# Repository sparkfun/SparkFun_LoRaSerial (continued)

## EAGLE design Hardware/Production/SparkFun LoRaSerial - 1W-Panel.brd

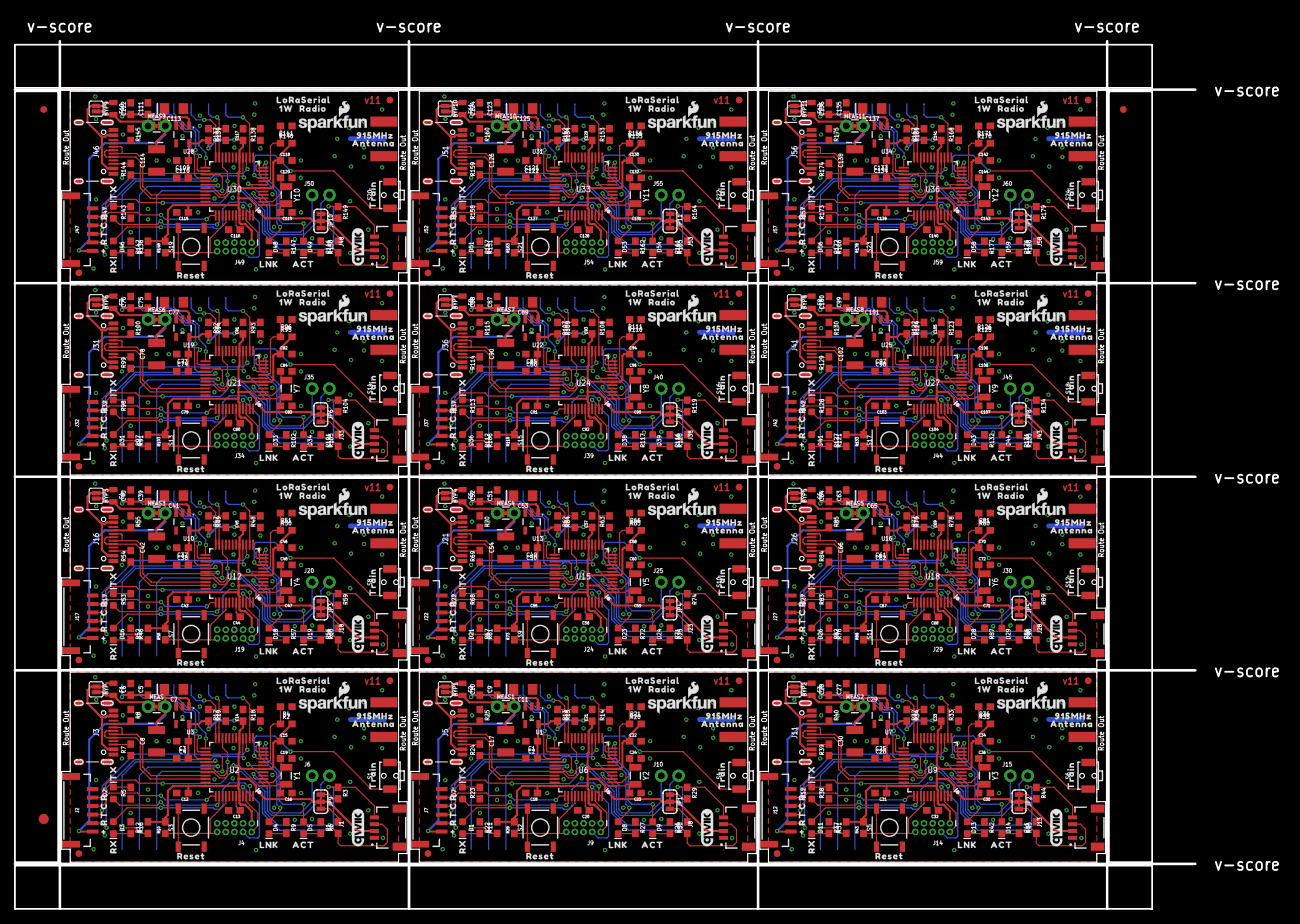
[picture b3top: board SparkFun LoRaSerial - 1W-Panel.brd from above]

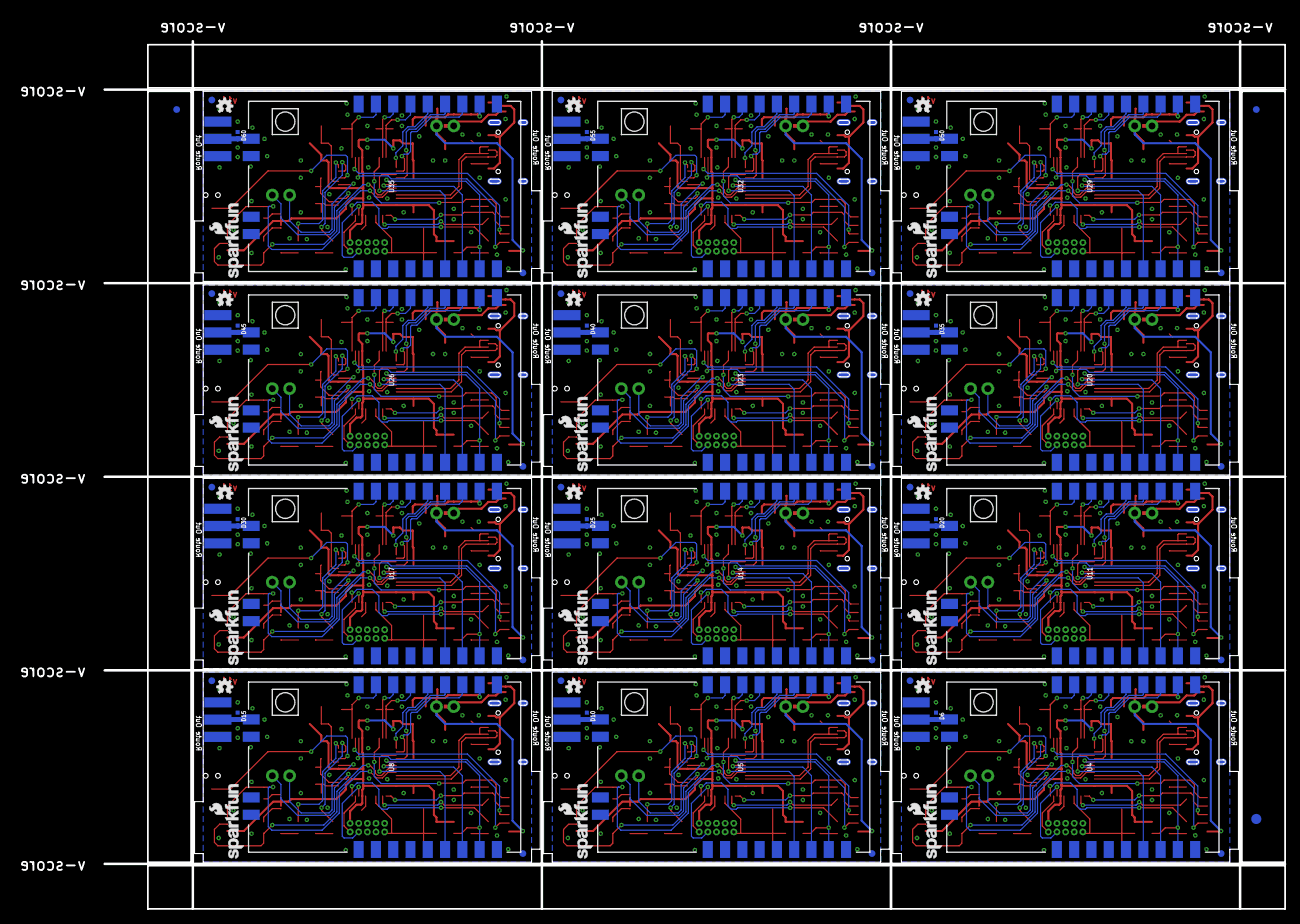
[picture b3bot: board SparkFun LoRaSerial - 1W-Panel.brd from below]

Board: 2 copper layers, 173.5 x 127.5 mm, 882 parts (87 on the bottom side), 540 nets.

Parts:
BYP, BYP1, BYP2, BYP3, BYP4, BYP5, BYP6, BYP7, BYP8, BYP9, BYP10, BYP11: JUMPER-SMT_2_NO_SILK; SMT-JUMPER_2_NO_SILK
C1, C3, C25, C37, C49, C61, C73, C85, C97, C109, C121, C133: 1.0uF; 0603
C2, C4, C6, C10, C12, C13, C14, C15, C18, C20, C21, C22, C26, C28, C31, C32, C33, C34, C38, C40, C43, C44, C45, C46, C50, C52, C55, C56, C57, C58, C62, C64, C67, C68, C69, C70, C74, C76, C79, C80, C81, C82, C86, C88, C91, C92, C93, C94, C98, C100, C103, C104, C105, C106, C110, C112, C115, C116, C117, C118, C122, C124, C127, C128, C129, C130, C134, C136, C139, C140, C141, C142: 0.1uF; 0603
C5, C9, C27, C39, C51, C63, C75, C87, C99, C111, C123, C135: 0.22uF; 0603
C7, C11, C29, C41, C53, C65, C77, C89, C101, C113, C125, C137: 10uF; EIA3216
C8, C17, C30, C42, C54, C66, C78, C90, C102, C114, C126, C138: 47uF; EIA3528
C16, C19, C23, C24, C35, C36, C47, C48, C59, C60, C71, C72, C83, C84, C95, C96, C107, C108, C119, C120, C131, C132, C143, C144: 15pF; 0603
D1, D3, D11, D16, D21, D26, D31, D36, D41, D46, D51, D56: Yellow; LED-0603
D2, D7, D12, D17, D22, D27, D32, D37, D42, D47, D52, D57: GREEN; LED-0603
D4, D8, D13, D18, D23, D28, D33, D38, D43, D48, D53, D58: BLUE; LED-0603
D5, D9, D14, D19, D24, D29, D34, D39, D44, D49, D54, D59: RED; LED-0603
D6, D10, D15, D20, D25, D30, D35, D40, D45, D50, D55, D60: PESD0402; 0402-TIGHT
E1, E2, E3, E4, E5, E6, E7, E8, E9, E10, E11, E12: RP-SMA; RP-SMA-EDGE
E$1, E$2, E$3, E$4: FIDUCIAL-1X2
E$5, E$6: FIDUCIAL-1.5X3
F1, F2, F3, F4, F5, F6, F7, F8, F9, F10, F11, F12: 6V 0.5A; 0805
FID1, FID2, FID3, FID4, FID5, FID6, FID7, FID8, FID9, FID10, FID11, FID12, FID13, FID14, FID15, FID16, FID17, FID18, FID19, FID20, FID21, FID22, FID23, FID24, FID25, FID26, FID27, FID28, FID29, FID30, FID31, FID32, FID33, FID34, FID35, FID36, FID37, FID38, FID39, FID40, FID41, FID42, FID43, FID44, FID45, FID46, FID47, FID48: FIDUCIAL1X2; FIDUCIAL-1X2
J1, J8, J13, J18, J23, J28, J33, J38, J43, J48, J53, J58: QWIIC_RIGHT_ANGLE; JST04_1MM_RA
J2, J7, J12, J17, J22, J27, J32, J37, J42, J47, J52, J57: JST-6-SMD-1.25MM-LOCKING
J3, J5, J11, J16, J21, J26, J31, J36, J41, J46, J51, J56: USB C; USB-C-16P
J4, J9, J14, J19, J24, J29, J34, J39, J44, J49, J54, J59: JTAG; 2X5-PTH-1.27MM-NO_SILK
J6, J10, J15, J20, J25, J30, J35, J40, J45, J50, J55, J60: 1X02_NO_SILK
JP1, JP2, JP3, JP4, JP5, JP6, JP7, JP8, JP9, JP10, JP11, JP12: JUMPER-SMT_3_2-NC_TRACE_SILK; SMT-JUMPER_3_2-NC_TRACE_SILK
LOGO1, LOGO5, LOGO9, LOGO13, LOGO17, LOGO21, LOGO25, LOGO29, LOGO33, LOGO37, LOGO41, LOGO45: SFE_LOGO_NAME_FLAME10_MM; SFE_LOGO_NAME_FLAME_10MM
LOGO2, LOGO6, LOGO10, LOGO14, LOGO18, LOGO22, LOGO26, LOGO30, LOGO34, LOGO38, LOGO42, LOGO46: SFE_LOGO_NAME_FLAME.1_INCH; SFE_LOGO_NAME_FLAME_.1
LOGO3, LOGO8, LOGO12, LOGO16, LOGO20, LOGO24, LOGO28, LOGO32, LOGO36, LOGO40, LOGO44, LOGO48: QWIIC_LOGO_CONNECTOR; QWIIC_5.5MM
LOGO4, LOGO7, LOGO11, LOGO15, LOGO19, LOGO23, LOGO27, LOGO31, LOGO35, LOGO39, LOGO43, LOGO47: OSHW-LOGOMINI; OSHW-LOGO-MINI
MEAS, MEAS1, MEAS2, MEAS3, MEAS4, MEAS5, MEAS6, MEAS7, MEAS8, MEAS9, MEAS10, MEAS11: JUMPER-COMBO_2_NC_TRACE; COMBO-JUMPER_2_NC_TRACE
R1, R9, R26, R27, R41, R42, R56, R57, R71, R72, R86, R87, R101, R102, R116, R117, R131, R132, R146, R147, R161, R162, R176, R177: 1k; 0603
R2, R4, R10, R20, R21, R28, R35, R36, R43, R50, R51, R58, R65, R66, R73, R80, R81, R88, R95, R96, R103, R110, R111, R118, R125, R126, R133, R140, R141, R148, R155, R156, R163, R170, R171, R178: 10k; 0603
R3, R6, R29, R30, R44, R45, R59, R60, R74, R75, R89, R90, R104, R105, R119, R120, R134, R135, R149, R150, R164, R165, R179, R180: 2.2k; 0603
R5, R12, R22, R23, R37, R38, R52, R53, R67, R68, R82, R83, R97, R98, R112, R113, R127, R128, R142, R143, R157, R158, R172, R173: 4.7k; 0603
R7, R8, R24, R25, R39, R40, R54, R55, R69, R70, R84, R85, R99, R100, R114, R115, R129, R130, R144, R145, R159, R160, R174, R175: 5.1k; 0603
R11, R13, R14, R15, R16, R17, R18, R19, R31, R32, R33, R34, R46, R47, R48, R49, R61, R62, R63, R64, R76, R77, R78, R79, R91, R92, R93, R94, R106, R107, R108, R109, R121, R122, R123, R124, R136, R137, R138, R139, R151, R152, R153, R154, R166, R167, R168, R169: 100k; 0603
S1, S4, S6, S8, S10, S12, S14, S16, S18, S20, S22, S24: Train; TACTILE_SWITCH_SMD_RIGHT_ANGLE
S2, S3, S5, S7, S9, S11, S13, S15, S17, S19, S21, S23: Reset; TACTILE_SWITCH_SMD_5.2MM
U1, U3, U7, U10, U13, U16, U19, U22, U25, U28, U31, U34: AP2112K-3.3; SOT23-5
U2, U6, U9, U12, U15, U18, U21, U24, U27, U30, U33, U36: ATSAMD21G-A; TQFP-48
U4, U5, U8, U11, U14, U17, U20, U23, U26, U29, U32, U35: E19-915M30S; E19-915MS1W
U$1, U$33, U$50, U$67, U$84, U$101, U$118, U$135, U$152, U$169, U$186, U$203: 1W1
U$2, U$8, U$35, U$52, U$69, U$86, U$103, U$120, U$137, U$154, U$171, U$188: RESET0
U$3, U$19, U$36, U$53, U$70, U$87, U$104, U$121, U$138, U$155, U$172, U$189: 915MHZ0
U$4, U$34, U$51, U$68, U$85, U$102, U$119, U$136, U$153, U$170, U$187, U$204: TRAIN0
U$5, U$21, U$38, U$55, U$72, U$89, U$106, U$123, U$140, U$157, U$174, U$191: RADIO2
U$6, U$22, U$39, U$56, U$73, U$90, U$107, U$124, U$141, U$158, U$175, U$192: ACT3
U$7, U$23, U$40, U$57, U$74, U$91, U$108, U$125, U$142, U$159, U$176, U$193: LNK2
U$9, U$20, U$37, U$54, U$71, U$88, U$105, U$122, U$139, U$156, U$173, U$190: ANTENNA1
U$10, U$24, U$41, U$58, U$75, U$92, U$109, U$126, U$143, U$160, U$177, U$194: RX1
U$11, U$25, U$42, U$59, U$76, U$93, U$110, U$127, U$144, U$161, U$178, U$195: TX0
U$12, U$26, U$43, U$60, U$77, U$94, U$111, U$128, U$145, U$162, U$179, U$196: #0
U$13, U$27, U$44, U$61, U$78, U$95, U$112, U$129, U$146, U$163, U$180, U$197: #1
U$14, U$28, U$45, U$62, U$79, U$96, U$113, U$130, U$147, U$164, U$181, U$198: R3
U$15, U$29, U$46, U$63, U$80, U$97, U$114, U$131, U$148, U$165, U$182, U$199: T2
U$16, U$30, U$47, U$64, U$81, U$98, U$115, U$132, U$149, U$166, U$183, U$200: C0
U$17, U$31, U$48, U$65, U$82, U$99, U$116, U$133, U$150, U$167, U$184, U$201: R1
U$18, U$32, U$49, U$66, U$83, U$100, U$117, U$134, U$151, U$168, U$185, U$202: LORASERIAL0
Y1, Y2, Y3, Y4, Y5, Y6, Y7, Y8, Y9, Y10, Y11, Y12: 32.768kHz; CRYSTAL-SMD-3.2X1.5MM

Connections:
3.3V: C3.1, C4.2, C12.1, C14.1, C15.1, J1.2, J4.1, JP9.2, R2.2, R10.2, R16.2, R17.2, U2.6, U2.17, U2.36, U2.44, U3.5
3.3V1: C1.1, C2.2, C18.1, C21.1, C22.1, J8.2, J9.1, JP1.2, R11.2, R13.2, R20.2, R28.2, U1.5, U6.6, U6.17, U6.36, U6.44
3.3V2: C25.1, C26.2, C31.1, C33.1, C34.1, J13.2, J14.1, JP2.2, R31.2, R32.2, R35.2, R43.2, U7.5, U9.6, U9.17, U9.36, U9.44
3.3V3: C37.1, C38.2, C43.1, C45.1, C46.1, J18.2, J19.1, JP3.2, R46.2, R47.2, R50.2, R58.2, U10.5, U12.6, U12.17, U12.36, U12.44
3.3V4: C49.1, C50.2, C55.1, C57.1, C58.1, J23.2, J24.1, JP4.2, R61.2, R62.2, R65.2, R73.2, U13.5, U15.6, U15.17, U15.36, U15.44
3.3V5: C61.1, C62.2, C67.1, C69.1, C70.1, J28.2, J29.1, JP5.2, R76.2, R77.2, R80.2, R88.2, U16.5, U18.6, U18.17, U18.36, U18.44
3.3V6: C73.1, C74.2, C79.1, C81.1, C82.1, J33.2, J34.1, JP6.2, R91.2, R92.2, R95.2, R103.2, U19.5, U21.6, U21.17, U21.36, U21.44
3.3V7: C85.1, C86.2, C91.1, C93.1, C94.1, J38.2, J39.1, JP7.2, R106.2, R107.2, R110.2, R118.2, U22.5, U24.6, U24.17, U24.36, U24.44
3.3V8: C97.1, C98.2, C103.1, C105.1, C106.1, J43.2, J44.1, JP8.2, R121.2, R122.2, R125.2, R133.2, U25.5, U27.6, U27.17, U27.36, U27.44
3.3V9: C109.1, C110.2, C115.1, C117.1, C118.1, J48.2, J49.1, JP10.2, R136.2, R137.2, R140.2, R148.2, U28.5, U30.6, U30.17, U30.36, U30.44
3.3V10: C121.1, C122.2, C127.1, C129.1, C130.1, J53.2, J54.1, JP11.2, R151.2, R152.2, R155.2, R163.2, U31.5, U33.6, U33.17, U33.36, U33.44
3.3V11: C133.1, C134.2, C139.1, C141.1, C142.1, J58.2, J59.1, JP12.2, R166.2, R167.2, R170.2, R178.2, U34.5, U36.6, U36.17, U36.36, U36.44
5V: C5.1, C6.1, C7.+, C8.A, J2.6, MEAS.2, MEAS.4, U3.1, U3.3, U4.11
5V1: C9.1, C10.1, C11.+, C17.A, J7.6, MEAS1.2, MEAS1.4, U1.1, U1.3, U5.11
5V2: C27.1, C28.1, C29.+, C30.A, J12.6, MEAS2.2, MEAS2.4, U7.1, U7.3, U8.11
5V3: C39.1, C40.1, C41.+, C42.A, J17.6, MEAS3.2, MEAS3.4, U10.1, U10.3, U11.11
5V4: C51.1, C52.1, C53.+, C54.A, J22.6, MEAS4.2, MEAS4.4, U13.1, U13.3, U14.11
5V5: C63.1, C64.1, C65.+, C66.A, J27.6, MEAS5.2, MEAS5.4, U16.1, U16.3, U17.11
5V6: C75.1, C76.1, C77.+, C78.A, J32.6, MEAS6.2, MEAS6.4, U19.1, U19.3, U20.11
5V7: C87.1, C88.1, C89.+, C90.A, J37.6, MEAS7.2, MEAS7.4, U22.1, U22.3, U23.11
5V8: C99.1, C100.1, C101.+, C102.A, J42.6, MEAS8.2, MEAS8.4, U25.1, U25.3, U26.11
5V9: C111.1, C112.1, C113.+, C114.A, J47.6, MEAS9.2, MEAS9.4, U28.1, U28.3, U29.11
5V10: C123.1, C124.1, C125.+, C126.A, J52.6, MEAS10.2, MEAS10.4, U31.1, U31.3, U32.11
5V11: C135.1, C136.1, C137.+, C138.A, J57.6, MEAS11.2, MEAS11.4, U34.1, U34.3, U35.11
A0: J6.2, U2.3
A1: J6.1, U2.7
A2: J10.1, U6.7
A2/BOARD_ID: R2.1, R4.2, U2.8
A2/BOARD_ID1: R20.1, R21.2, U6.8
A2/BOARD_ID2: R35.1, R36.2, U9.8
A2/BOARD_ID3: R50.1, R51.2, U12.8
A2/BOARD_ID4: R65.1, R66.2, U15.8
A2/BOARD_ID5: R80.1, R81.2, U18.8
A2/BOARD_ID6: R95.1, R96.2, U21.8
A2/BOARD_ID7: R110.1, R111.2, U24.8
A2/BOARD_ID8: R125.1, R126.2, U27.8
A2/BOARD_ID9: R140.1, R141.2, U30.8
A2/BOARD_ID10: R155.1, R156.2, U33.8
A2/BOARD_ID11: R170.1, R171.2, U36.8
A3: J10.2, U6.3
A3/TRAIN: S1.1, U2.9
A3/TRAIN1: S4.1, U6.9
A3/TRAIN2: S6.1, U9.9
A3/TRAIN3: S8.1, U12.9
A3/TRAIN4: S10.1, U15.9
A3/TRAIN5: S12.1, U18.9
A3/TRAIN6: S14.1, U21.9
A3/TRAIN7: S16.1, U24.9
A3/TRAIN8: S18.1, U27.9
A3/TRAIN9: S20.1, U30.9
A3/TRAIN10: S22.1, U33.9
A3/TRAIN11: S24.1, U36.9
A5/RX_LED: D3.A, U2.47
A5/RX_LED1: D1.A, U6.47
A5/RX_LED2: D11.A, U9.47
A5/RX_LED3: D16.A, U12.47
A5/RX_LED4: D21.A, U15.47
A5/RX_LED5: D26.A, U18.47
A5/RX_LED6: D31.A, U21.47
A5/RX_LED7: D36.A, U24.47
A5/RX_LED8: D41.A, U27.47
A5/RX_LED9: D46.A, U30.47
A5/RX_LED10: D51.A, U33.47
A5/RX_LED11: D56.A, U36.47
A6: J15.1, U9.7
A7: J15.2, U9.3
A9: J20.1, U12.7
A10: J20.2, U12.3
A12: J25.1, U15.7
A13: J25.2, U15.3
A15: J30.1, U18.7
A16: J30.2, U18.3
A18: J35.1, U21.7
A19: J35.2, U21.3
A21: J40.1, U24.7
A22: J40.2, U24.3
A24: J45.1, U27.7
A25: J45.2, U27.3
A27: J50.1, U30.7
A28: J50.2, U30.3
A30: J55.1, U33.7
A31: J55.2, U33.3
A33: J60.1, U36.7
A34: J60.2, U36.3
CC1: J3.A5, R8.2
CC2: J3.B5, R7.2
CC3: J5.B5, R24.2
CC4: J5.A5, R25.2
CC5: J11.B5, R39.2
CC6: J11.A5, R40.2
CC7: J16.B5, R54.2
CC8: J16.A5, R55.2
CC9: J21.B5, R69.2
CC10: J21.A5, R70.2
CC11: J26.B5, R84.2
CC12: J26.A5, R85.2
CC13: J31.B5, R99.2
CC14: J31.A5, R100.2
CC15: J36.B5, R114.2
CC16: J36.A5, R115.2
CC17: J41.B5, R129.2
CC18: J41.A5, R130.2
CC19: J46.B5, R144.2
CC20: J46.A5, R145.2
CC21: J51.B5, R159.2
CC22: J51.A5, R160.2
CC23: J56.B5, R174.2
CC24: J56.A5, R175.2
D2/LORA_TXEN: R19.2, U2.23, U4.16
D2/LORA_TXEN1: R15.2, U5.16, U6.23
D2/LORA_TXEN2: R34.2, U8.16, U9.23
D2/LORA_TXEN3: R49.2, U11.16, U12.23
D2/LORA_TXEN4: R64.2, U14.16, U15.23
D2/LORA_TXEN5: R79.2, U17.16, U18.23
D2/LORA_TXEN6: R94.2, U20.16, U21.23
D2/LORA_TXEN7: R109.2, U23.16, U24.23
D2/LORA_TXEN8: R124.2, U26.16, U27.23
D2/LORA_TXEN9: R139.2, U29.16, U30.23
D2/LORA_TXEN10: R154.2, U32.16, U33.23
D2/LORA_TXEN11: R169.2, U35.16, U36.23
D3/LORA_RXEN: R18.2, U2.14, U4.17
D3/LORA_RXEN1: R14.2, U5.17, U6.14
D3/LORA_RXEN2: R33.2, U8.17, U9.14
D3/LORA_RXEN3: R48.2, U11.17, U12.14
D3/LORA_RXEN4: R63.2, U14.17, U15.14
D3/LORA_RXEN5: R78.2, U17.17, U18.14
D3/LORA_RXEN6: R93.2, U20.17, U21.14
D3/LORA_RXEN7: R108.2, U23.17, U24.14
D3/LORA_RXEN8: R123.2, U26.17, U27.14
D3/LORA_RXEN9: R138.2, U29.17, U30.14
D3/LORA_RXEN10: R153.2, U32.17, U33.14
D3/LORA_RXEN11: R168.2, U35.17, U36.14
D5/LORA_!CS!: R17.1, U2.24, U4.15
D5/LORA_!CS!1: R13.1, U5.15, U6.24
D5/LORA_!CS!2: R32.1, U8.15, U9.24
D5/LORA_!CS!3: R47.1, U11.15, U12.24
D5/LORA_!CS!4: R62.1, U14.15, U15.24
D5/LORA_!CS!5: R77.1, U17.15, U18.24
D5/LORA_!CS!6: R92.1, U20.15, U21.24
D5/LORA_!CS!7: R107.1, U23.15, U24.24
D5/LORA_!CS!8: R122.1, U26.15, U27.24
D5/LORA_!CS!9: R137.1, U29.15, U30.24
D5/LORA_!CS!10: R152.1, U32.15, U33.24
D5/LORA_!CS!11: R167.1, U35.15, U36.24
D6/LORA_!RST!: R16.1, U2.29, U4.8
D6/LORA_!RST!1: R11.1, U5.8, U6.29
D6/LORA_!RST!2: R31.1, U8.8, U9.29
D6/LORA_!RST!3: R46.1, U11.8, U12.29
D6/LORA_!RST!4: R61.1, U14.8, U15.29
D6/LORA_!RST!5: R76.1, U17.8, U18.29
D6/LORA_!RST!6: R91.1, U20.8, U21.29
D6/LORA_!RST!7: R106.1, U23.8, U24.29
D6/LORA_!RST!8: R121.1, U26.8, U27.29
D6/LORA_!RST!9: R136.1, U29.8, U30.29
D6/LORA_!RST!10: R151.1, U32.8, U33.29
D6/LORA_!RST!11: R166.1, U35.8, U36.29
D7/LORA_D0: U2.30, U4.7
D7/LORA_D1: U5.7, U6.30
D7/LORA_D2: U8.7, U9.30
D7/LORA_D3: U11.7, U12.30
D7/LORA_D4: U14.7, U15.30
D7/LORA_D5: U17.7, U18.30
D7/LORA_D6: U20.7, U21.30
D7/LORA_D7: U23.7, U24.30
D7/LORA_D8: U26.7, U27.30
D7/LORA_D9: U29.7, U30.30
D7/LORA_D10: U32.7, U33.30
D7/LORA_D11: U35.7, U36.30
D8/LINK: D4.A, U2.11
D8/LINK1: D8.A, U6.11
D8/LINK2: D13.A, U9.11
D8/LINK3: D18.A, U12.11
D8/LINK4: D23.A, U15.11
D8/LINK5: D28.A, U18.11
D8/LINK6: D33.A, U21.11
D8/LINK7: D38.A, U24.11
D8/LINK8: D43.A, U27.11
D8/LINK9: D48.A, U30.11
D8/LINK10: D53.A, U33.11
D8/LINK11: D58.A, U36.11
D9/ACT: D5.A, U2.12
D9/ACT1: D9.A, U6.12
D9/ACT2: D14.A, U9.12
D9/ACT3: D19.A, U12.12
D9/ACT4: D24.A, U15.12
D9/ACT5: D29.A, U18.12
D9/ACT6: D34.A, U21.12
D9/ACT7: D39.A, U24.12
D9/ACT8: D44.A, U27.12
D9/ACT9: D49.A, U30.12
D9/ACT10: D54.A, U33.12
D9/ACT11: D59.A, U36.12
D10/LORA_D1: U2.27, U4.6
D10/LORA_D2: U5.6, U6.27
D10/LORA_D3: U8.6, U9.27
D10/LORA_D4: U11.6, U12.27
D10/LORA_D5: U14.6, U15.27
D10/LORA_D6: U17.6, U18.27
D10/LORA_D7: U20.6, U21.27
D10/LORA_D8: U23.6, U24.27
D10/LORA_D9: U26.6, U27.27
D10/LORA_D10: U29.6, U30.27
D10/LORA_D11: U32.6, U33.27
D10/LORA_D12: U35.6, U36.27
D11/SPI_PICO: U2.25, U4.14
D11/SPI_PICO1: U5.14, U6.25
D11/SPI_PICO2: U8.14, U9.25
D11/SPI_PICO3: U11.14, U12.25
D11/SPI_PICO4: U14.14, U15.25
D11/SPI_PICO5: U17.14, U18.25
D11/SPI_PICO6: U20.14, U21.25
D11/SPI_PICO7: U23.14, U24.25
D11/SPI_PICO8: U26.14, U27.25
D11/SPI_PICO9: U29.14, U30.25
D11/SPI_PICO10: U32.14, U33.25
D11/SPI_PICO11: U35.14, U36.25
D12/SPI_POCI: U2.28, U4.13
D12/SPI_POCI1: U5.13, U6.28
D12/SPI_POCI2: U8.13, U9.28
D12/SPI_POCI3: U11.13, U12.28
D12/SPI_POCI4: U14.13, U15.28
D12/SPI_POCI5: U17.13, U18.28
D12/SPI_POCI6: U20.13, U21.28
D12/SPI_POCI7: U23.13, U24.28
D12/SPI_POCI8: U26.13, U27.28
D12/SPI_POCI9: U29.13, U30.28
D12/SPI_POCI10: U32.13, U33.28
D12/SPI_POCI11: U35.13, U36.28
D13/SPI_SCK: U2.26, U4.12
D13/SPI_SCK1: U5.12, U6.26
D13/SPI_SCK2: U8.12, U9.26
D13/SPI_SCK3: U11.12, U12.26
D13/SPI_SCK4: U14.12, U15.26
D13/SPI_SCK5: U17.12, U18.26
D13/SPI_SCK6: U20.12, U21.26
D13/SPI_SCK7: U23.12, U24.26
D13/SPI_SCK8: U26.12, U27.26
D13/SPI_SCK9: U29.12, U30.26
D13/SPI_SCK10: U32.12, U33.26
D13/SPI_SCK11: U35.12, U36.26
D20/SDA: J1.3, R6.1, U2.31
D20/SDA1: J8.3, R30.1, U6.31
D20/SDA2: J13.3, R45.1, U9.31
D20/SDA3: J18.3, R60.1, U12.31
D20/SDA4: J23.3, R75.1, U15.31
D20/SDA5: J28.3, R90.1, U18.31
D20/SDA6: J33.3, R105.1, U21.31
D20/SDA7: J38.3, R120.1, U24.31
D20/SDA8: J43.3, R135.1, U27.31
D20/SDA9: J48.3, R150.1, U30.31
D20/SDA10: J53.3, R165.1, U33.31
D20/SDA11: J58.3, R180.1, U36.31
D21/SCL: J1.4, R3.1, U2.32
D21/SCL1: J8.4, R29.1, U6.32
D21/SCL2: J13.4, R44.1, U9.32
D21/SCL3: J18.4, R59.1, U12.32
D21/SCL4: J23.4, R74.1, U15.32
D21/SCL5: J28.4, R89.1, U18.32
D21/SCL6: J33.4, R104.1, U21.32
D21/SCL7: J38.4, R119.1, U24.32
D21/SCL8: J43.4, R134.1, U27.32
D21/SCL9: J48.4, R149.1, U30.32
D21/SCL10: J53.4, R164.1, U33.32
D21/SCL11: J58.4, R179.1, U36.32
D28/USB_D-: J3.A7, J3.B7, U2.33
D28/USB_D-1: J5.A7, J5.B7, U6.33
D28/USB_D-2: J11.A7, J11.B7, U9.33
D28/USB_D-3: J16.A7, J16.B7, U12.33
D28/USB_D-4: J21.A7, J21.B7, U15.33
D28/USB_D-5: J26.A7, J26.B7, U18.33
D28/USB_D-6: J31.A7, J31.B7, U21.33
D28/USB_D-7: J36.A7, J36.B7, U24.33
D28/USB_D-8: J41.A7, J41.B7, U27.33
D28/USB_D-9: J46.A7, J46.B7, U30.33
D28/USB_D-10: J51.A7, J51.B7, U33.33
D28/USB_D-11: J56.A7, J56.B7, U36.33
D29/USB_D+: J3.A6, J3.B6, U2.34
D29/USB_D+1: J5.A6, J5.B6, U6.34
D29/USB_D+2: J11.A6, J11.B6, U9.34
D29/USB_D+3: J16.A6, J16.B6, U12.34
D29/USB_D+4: J21.A6, J21.B6, U15.34
D29/USB_D+5: J26.A6, J26.B6, U18.34
D29/USB_D+6: J31.A6, J31.B6, U21.34
D29/USB_D+7: J36.A6, J36.B6, U24.34
D29/USB_D+8: J41.A6, J41.B6, U27.34
D29/USB_D+9: J46.A6, J46.B6, U30.34
D29/USB_D+10: J51.A6, J51.B6, U33.34
D29/USB_D+11: J56.A6, J56.B6, U36.34
D30/CTS-I: J2.3, U2.37
D30/CTS-I1: J7.3, U6.37
D30/CTS-I2: J12.3, U9.37
D30/CTS-I3: J17.3, U12.37
D30/CTS-I4: J22.3, U15.37
D30/CTS-I5: J27.3, U18.37
D30/CTS-I6: J32.3, U21.37
D30/CTS-I7: J37.3, U24.37
D30/CTS-I8: J42.3, U27.37
D30/CTS-I9: J47.3, U30.37
D30/CTS-I10: J52.3, U33.37
D30/CTS-I11: J57.3, U36.37
D31/TX_LED: D2.A, U2.38
D31/TX_LED1: D7.A, U6.38
D31/TX_LED2: D12.A, U9.38
D31/TX_LED3: D17.A, U12.38
D31/TX_LED4: D22.A, U15.38
D31/TX_LED5: D27.A, U18.38
D31/TX_LED6: D32.A, U21.38
D31/TX_LED7: D37.A, U24.38
D31/TX_LED8: D42.A, U27.38
D31/TX_LED9: D47.A, U30.38
D31/TX_LED10: D52.A, U33.38
D31/TX_LED11: D57.A, U36.38
D38/RTS-O: J2.2, U2.22
D38/RTS-O1: J7.2, U6.22
D38/RTS-O2: J12.2, U9.22
D38/RTS-O3: J17.2, U12.22
D38/RTS-O4: J22.2, U15.22
D38/RTS-O5: J27.2, U18.22
D38/RTS-O6: J32.2, U21.22
D38/RTS-O7: J37.2, U24.22
D38/RTS-O8: J42.2, U27.22
D38/RTS-O9: J47.2, U30.22
D38/RTS-O10: J52.2, U33.22
D38/RTS-O11: J57.2, U36.22
GND: C3.2, C4.1, C5.2, C6.2, C7.-, C8.C, C12.2, C13.2, C14.2, C15.2, C16.1, C19.2, D6.1, E2.GND@0, E2.GND@1, E2.GND@2, E2.GND@3, J1.1, J2.1, J3.GND, J3.GND2, J4.3, J4.5, J4.9, R1.1, R4.1, R5.1, R7.1, R8.1, R9.1, R12.1, R18.1, R19.1, S1.2, S3.3, S3.4, U2.5, U2.18, U2.35, U2.42, U3.2, U4.1, U4.9, U4.10, U4.18, U4.20, U4.21, U4.22
GND1: C1.2, C2.1, C9.2, C10.2, C11.-, C17.C, C18.2, C20.2, C21.2, C22.2, C23.1, C24.2, D10.1, E1.GND@0, E1.GND@1, E1.GND@2, E1.GND@3, J5.GND, J5.GND2, J7.1, J8.1, J9.3, J9.5, J9.9, R14.1, R15.1, R21.1, R22.1, R23.1, R24.1, R25.1, R26.1, R27.1, S2.3, S2.4, S4.2, U1.2, U5.1, U5.9, U5.10, U5.18, U5.20, U5.21, U5.22, U6.5, U6.18, U6.35, U6.42
GND2: C25.2, C26.1, C27.2, C28.2, C29.-, C30.C, C31.2, C32.2, C33.2, C34.2, C35.1, C36.2, D15.1, E3.GND@0, E3.GND@1, E3.GND@2, E3.GND@3, J11.GND, J11.GND2, J12.1, J13.1, J14.3, J14.5, J14.9, R33.1, R34.1, R36.1, R37.1, R38.1, R39.1, R40.1, R41.1, R42.1, S5.3, S5.4, S6.2, U7.2, U8.1, U8.9, U8.10, U8.18, U8.20, U8.21, U8.22, U9.5, U9.18, U9.35, U9.42
GND3: C37.2, C38.1, C39.2, C40.2, C41.-, C42.C, C43.2, C44.2, C45.2, C46.2, C47.1, C48.2, D20.1, E4.GND@0, E4.GND@1, E4.GND@2, E4.GND@3, J16.GND, J16.GND2, J17.1, J18.1, J19.3, J19.5, J19.9, R48.1, R49.1, R51.1, R52.1, R53.1, R54.1, R55.1, R56.1, R57.1, S7.3, S7.4, S8.2, U10.2, U11.1, U11.9, U11.10, U11.18, U11.20, U11.21, U11.22, U12.5, U12.18, U12.35, U12.42
GND4: C49.2, C50.1, C51.2, C52.2, C53.-, C54.C, C55.2, C56.2, C57.2, C58.2, C59.1, C60.2, D25.1, E5.GND@0, E5.GND@1, E5.GND@2, E5.GND@3, J21.GND, J21.GND2, J22.1, J23.1, J24.3, J24.5, J24.9, R63.1, R64.1, R66.1, R67.1, R68.1, R69.1, R70.1, R71.1, R72.1, S9.3, S9.4, S10.2, U13.2, U14.1, U14.9, U14.10, U14.18, U14.20, U14.21, U14.22, U15.5, U15.18, U15.35, U15.42
GND5: C61.2, C62.1, C63.2, C64.2, C65.-, C66.C, C67.2, C68.2, C69.2, C70.2, C71.1, C72.2, D30.1, E6.GND@0, E6.GND@1, E6.GND@2, E6.GND@3, J26.GND, J26.GND2, J27.1, J28.1, J29.3, J29.5, J29.9, R78.1, R79.1, R81.1, R82.1, R83.1, R84.1, R85.1, R86.1, R87.1, S11.3, S11.4, S12.2, U16.2, U17.1, U17.9, U17.10, U17.18, U17.20, U17.21, U17.22, U18.5, U18.18, U18.35, U18.42
GND6: C73.2, C74.1, C75.2, C76.2, C77.-, C78.C, C79.2, C80.2, C81.2, C82.2, C83.1, C84.2, D35.1, E7.GND@0, E7.GND@1, E7.GND@2, E7.GND@3, J31.GND, J31.GND2, J32.1, J33.1, J34.3, J34.5, J34.9, R93.1, R94.1, R96.1, R97.1, R98.1, R99.1, R100.1, R101.1, R102.1, S13.3, S13.4, S14.2, U19.2, U20.1, U20.9, U20.10, U20.18, U20.20, U20.21, U20.22, U21.5, U21.18, U21.35, U21.42
GND7: C85.2, C86.1, C87.2, C88.2, C89.-, C90.C, C91.2, C92.2, C93.2, C94.2, C95.1, C96.2, D40.1, E8.GND@0, E8.GND@1, E8.GND@2, E8.GND@3, J36.GND, J36.GND2, J37.1, J38.1, J39.3, J39.5, J39.9, R108.1, R109.1, R111.1, R112.1, R113.1, R114.1, R115.1, R116.1, R117.1, S15.3, S15.4, S16.2, U22.2, U23.1, U23.9, U23.10, U23.18, U23.20, U23.21, U23.22, U24.5, U24.18, U24.35, U24.42
GND8: C97.2, C98.1, C99.2, C100.2, C101.-, C102.C, C103.2, C104.2, C105.2, C106.2, C107.1, C108.2, D45.1, E9.GND@0, E9.GND@1, E9.GND@2, E9.GND@3, J41.GND, J41.GND2, J42.1, J43.1, J44.3, J44.5, J44.9, R123.1, R124.1, R126.1, R127.1, R128.1, R129.1, R130.1, R131.1, R132.1, S17.3, S17.4, S18.2, U25.2, U26.1, U26.9, U26.10, U26.18, U26.20, U26.21, U26.22, U27.5, U27.18, U27.35, U27.42
GND9: C109.2, C110.1, C111.2, C112.2, C113.-, C114.C, C115.2, C116.2, C117.2, C118.2, C119.1, C120.2, D50.1, E10.GND@0, E10.GND@1, E10.GND@2, E10.GND@3, J46.GND, J46.GND2, J47.1, J48.1, J49.3, J49.5, J49.9, R138.1, R139.1, R141.1, R142.1, R143.1, R144.1, R145.1, R146.1, R147.1, S19.3, S19.4, S20.2, U28.2, U29.1, U29.9, U29.10, U29.18, U29.20, U29.21, U29.22, U30.5, U30.18, U30.35, U30.42
GND10: C121.2, C122.1, C123.2, C124.2, C125.-, C126.C, C127.2, C128.2, C129.2, C130.2, C131.1, C132.2, D55.1, E11.GND@0, E11.GND@1, E11.GND@2, E11.GND@3, J51.GND, J51.GND2, J52.1, J53.1, J54.3, J54.5, J54.9, R153.1, R154.1, R156.1, R157.1, R158.1, R159.1, R160.1, R161.1, R162.1, S21.3, S21.4, S22.2, U31.2, U32.1, U32.9, U32.10, U32.18, U32.20, U32.21, U32.22, U33.5, U33.18, U33.35, U33.42
GND11: C133.2, C134.1, C135.2, C136.2, C137.-, C138.C, C139.2, C140.2, C141.2, C142.2, C143.1, C144.2, D60.1, E12.GND@0, E12.GND@1, E12.GND@2, E12.GND@3, J56.GND, J56.GND2, J57.1, J58.1, J59.3, J59.5, J59.9, R168.1, R169.1, R171.1, R172.1, R173.1, R174.1, R175.1, R176.1, R177.1, S23.3, S23.4, S24.2, U34.2, U35.1, U35.9, U35.10, U35.18, U35.20, U35.21, U35.22, U36.5, U36.18, U36.35, U36.42
LORA_ANT: D6.2, E2.SIG, U4.19
LORA_ANT1: D10.2, E1.SIG, U5.19
LORA_ANT2: D15.2, E3.SIG, U8.19
LORA_ANT3: D20.2, E4.SIG, U11.19
LORA_ANT4: D25.2, E5.SIG, U14.19
LORA_ANT5: D30.2, E6.SIG, U17.19
LORA_ANT6: D35.2, E7.SIG, U20.19
LORA_ANT7: D40.2, E8.SIG, U23.19
LORA_ANT8: D45.2, E9.SIG, U26.19
LORA_ANT9: D50.2, E10.SIG, U29.19
LORA_ANT10: D55.2, E11.SIG, U32.19
LORA_ANT11: D60.2, E12.SIG, U35.19
unnamed: C19.1, U2.2, Y1.P$1
unnamed: C16.2, U2.1, Y1.P$2
unnamed: D3.C, R12.2
unnamed: D2.C, R5.2
unnamed: D9.C, R26.2
unnamed: D8.C, R27.2
unnamed: D5.C, R1.2
unnamed: D4.C, R9.2
unnamed: C23.2, U6.1, Y2.P$2
unnamed: C24.1, U6.2, Y2.P$1
unnamed: D1.C, R22.2
unnamed: D7.C, R23.2
unnamed: D14.C, R41.2
unnamed: D13.C, R42.2
unnamed: C35.2, U9.1, Y3.P$2
unnamed: C36.1, U9.2, Y3.P$1
unnamed: D11.C, R37.2
unnamed: D12.C, R38.2
unnamed: D19.C, R56.2
unnamed: D18.C, R57.2
unnamed: C47.2, U12.1, Y4.P$2
unnamed: C48.1, U12.2, Y4.P$1
unnamed: D16.C, R52.2
unnamed: D17.C, R53.2
unnamed: D24.C, R71.2
unnamed: D23.C, R72.2
unnamed: C59.2, U15.1, Y5.P$2
unnamed: C60.1, U15.2, Y5.P$1
unnamed: D21.C, R67.2
unnamed: D22.C, R68.2
unnamed: D29.C, R86.2
unnamed: D28.C, R87.2
unnamed: C71.2, U18.1, Y6.P$2
unnamed: C72.1, U18.2, Y6.P$1
unnamed: D26.C, R82.2
unnamed: D27.C, R83.2
unnamed: D34.C, R101.2
unnamed: D33.C, R102.2
unnamed: C83.2, U21.1, Y7.P$2
unnamed: C84.1, U21.2, Y7.P$1
unnamed: D31.C, R97.2
unnamed: D32.C, R98.2
unnamed: D39.C, R116.2
unnamed: D38.C, R117.2
unnamed: C95.2, U24.1, Y8.P$2
unnamed: C96.1, U24.2, Y8.P$1
unnamed: D36.C, R112.2
unnamed: D37.C, R113.2
unnamed: D44.C, R131.2
unnamed: D43.C, R132.2
unnamed: C107.2, U27.1, Y9.P$2
unnamed: C108.1, U27.2, Y9.P$1
unnamed: D41.C, R127.2
unnamed: D42.C, R128.2
unnamed: D49.C, R146.2
unnamed: D48.C, R147.2
unnamed: C119.2, U30.1, Y10.P$2
unnamed: C120.1, U30.2, Y10.P$1
unnamed: D46.C, R142.2
unnamed: D47.C, R143.2
unnamed: D54.C, R161.2
unnamed: D53.C, R162.2
unnamed: C131.2, U33.1, Y11.P$2
unnamed: C132.1, U33.2, Y11.P$1
unnamed: D51.C, R157.2
unnamed: D52.C, R158.2
unnamed: D59.C, R176.2
unnamed: D58.C, R177.2
unnamed: C143.2, U36.1, Y12.P$2
unnamed: C144.1, U36.2, Y12.P$1
unnamed: D56.C, R172.2
unnamed: D57.C, R173.2
RX-I: J2.5, U2.16
RX-I1: J7.5, U6.16
RX-I2: J12.5, U9.16
RX-I3: J17.5, U12.16
RX-I4: J22.5, U15.16
RX-I5: J27.5, U18.16
RX-I6: J32.5, U21.16
RX-I7: J37.5, U24.16
RX-I8: J42.5, U27.16
RX-I9: J47.5, U30.16
RX-I10: J52.5, U33.16
RX-I11: J57.5, U36.16
SAMD_!RESET!: J4.10, R10.1, S3.1, S3.2, U2.40
SAMD_!RESET!1: J9.10, R28.1, S2.1, S2.2, U6.40
SAMD_!RESET!2: J14.10, R43.1, S5.1, S5.2, U9.40
SAMD_!RESET!3: J19.10, R58.1, S7.1, S7.2, U12.40
SAMD_!RESET!4: J24.10, R73.1, S9.1, S9.2, U15.40
SAMD_!RESET!5: J29.10, R88.1, S11.1, S11.2, U18.40
SAMD_!RESET!6: J34.10, R103.1, S13.1, S13.2, U21.40
SAMD_!RESET!7: J39.10, R118.1, S15.1, S15.2, U24.40
SAMD_!RESET!8: J44.10, R133.1, S17.1, S17.2, U27.40
SAMD_!RESET!9: J49.10, R148.1, S19.1, S19.2, U30.40
SAMD_!RESET!10: J54.10, R163.1, S21.1, S21.2, U33.40
SAMD_!RESET!11: J59.10, R178.1, S23.1, S23.2, U36.40
SCL_PU1: JP9.1, R3.2
SCL_PU2: JP1.1, R29.2
SCL_PU3: JP2.1, R44.2
SCL_PU4: JP3.1, R59.2
SCL_PU5: JP4.1, R74.2
SCL_PU6: JP5.1, R89.2
SCL_PU7: JP6.1, R104.2
SCL_PU8: JP7.1, R119.2
SCL_PU9: JP8.1, R134.2
SCL_PU10: JP10.1, R149.2
SCL_PU11: JP11.1, R164.2
SCL_PU12: JP12.1, R179.2
SDA_PU1: JP9.3, R6.2
SDA_PU2: JP1.3, R30.2
SDA_PU3: JP2.3, R45.2
SDA_PU4: JP3.3, R60.2
SDA_PU5: JP4.3, R75.2
SDA_PU6: JP5.3, R90.2
SDA_PU7: JP6.3, R105.2
SDA_PU8: JP7.3, R120.2
SDA_PU9: JP8.3, R135.2
SDA_PU10: JP10.3, R150.2
SDA_PU11: JP11.3, R165.2
SDA_PU12: JP12.3, R180.2
SWCLK: J4.4, U2.45
SWCLK1: J9.4, U6.45
SWCLK2: J14.4, U9.45
SWCLK3: J19.4, U12.45
SWCLK4: J24.4, U15.45
SWCLK5: J29.4, U18.45
SWCLK6: J34.4, U21.45
SWCLK7: J39.4, U24.45
SWCLK8: J44.4, U27.45
SWCLK9: J49.4, U30.45
SWCLK10: J54.4, U33.45
SWCLK11: J59.4, U36.45
SWDIO: J4.2, U2.46
SWDIO1: J9.2, U6.46
SWDIO2: J14.2, U9.46
SWDIO3: J19.2, U12.46
SWDIO4: J24.2, U15.46
SWDIO5: J29.2, U18.46
SWDIO6: J34.2, U21.46
SWDIO7: J39.2, U24.46
SWDIO8: J44.2, U27.46
SWDIO9: J49.2, U30.46
SWDIO10: J54.2, U33.46
SWDIO11: J59.2, U36.46
TX-O: J2.4, U2.15
TX-O1: J7.4, U6.15
TX-O2: J12.4, U9.15
TX-O3: J17.4, U12.15
TX-O4: J22.4, U15.15
TX-O5: J27.4, U18.15
TX-O6: J32.4, U21.15
TX-O7: J37.4, U24.15
TX-O8: J42.4, U27.15
TX-O9: J47.4, U30.15
TX-O10: J52.4, U33.15
TX-O11: J57.4, U36.15
VDDCORE: C13.1, U2.43
VDDCORE1: C20.1, U6.43
VDDCORE2: C32.1, U9.43
VDDCORE3: C44.1, U12.43
VDDCORE4: C56.1, U15.43
VDDCORE5: C68.1, U18.43
VDDCORE6: C80.1, U21.43
VDDCORE7: C92.1, U24.43
VDDCORE8: C104.1, U27.43
VDDCORE9: C116.1, U30.43
VDDCORE10: C128.1, U33.43
VDDCORE11: C140.1, U36.43
VUSB: BYP.1, F1.1, J3.VBUS1, J3.VBUS2
VUSB1: BYP1.1, F2.1, J5.VBUS1, J5.VBUS2
VUSB2: BYP2.1, F3.1, J11.VBUS1, J11.VBUS2
VUSB3: BYP3.1, F4.1, J16.VBUS1, J16.VBUS2
VUSB4: BYP4.1, F5.1, J21.VBUS1, J21.VBUS2
VUSB5: BYP5.1, F6.1, J26.VBUS1, J26.VBUS2
VUSB6: BYP6.1, F7.1, J31.VBUS1, J31.VBUS2
VUSB7: BYP7.1, F8.1, J36.VBUS1, J36.VBUS2
VUSB8: BYP8.1, F9.1, J41.VBUS1, J41.VBUS2
VUSB9: BYP9.1, F10.1, J46.VBUS1, J46.VBUS2
VUSB10: BYP10.1, F11.1, J51.VBUS1, J51.VBUS2
VUSB11: BYP11.1, F12.1, J56.VBUS1, J56.VBUS2
V_USB: BYP.2, F1.2, MEAS.1, MEAS.3
V_USB1: BYP1.2, F2.2, MEAS1.1, MEAS1.3
V_USB2: BYP2.2, F3.2, MEAS2.1, MEAS2.3
V_USB3: BYP3.2, F4.2, MEAS3.1, MEAS3.3
V_USB4: BYP4.2, F5.2, MEAS4.1, MEAS4.3
V_USB5: BYP5.2, F6.2, MEAS5.1, MEAS5.3
V_USB6: BYP6.2, F7.2, MEAS6.1, MEAS6.3
V_USB7: BYP7.2, F8.2, MEAS7.1, MEAS7.3
V_USB8: BYP8.2, F9.2, MEAS8.1, MEAS8.3
V_USB9: BYP9.2, F10.2, MEAS9.1, MEAS9.3
V_USB10: BYP10.2, F11.2, MEAS10.1, MEAS10.3
V_USB11: BYP11.2, F12.2, MEAS11.1, MEAS11.3

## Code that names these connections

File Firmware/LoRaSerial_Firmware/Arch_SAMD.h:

#if defined(ARDUINO_ARCH_SAMD)
#ifndef __SAMD_H__

#include <FlashAsEEPROM_SAMD.h> //Click here to get the library: http://librarymanager/All#FlashStorage_SAMD21 v1.2.1 by Khoi Hoang
#include <WDTZero.h> //https://github.com/javos65/WDTZero
WDTZero myWatchDog;

#define NVM_ERASE_VALUE         0xff
#define NVM_UNIQUE_ID_OFFSET    (EEPROM_EMULATION_SIZE - (MAX_VC * UNIQUE_ID_BYTES))

/*
  Data flow
                   +--------------+
                   |     SAMD     |
                   |              |
    TTL Serial <-->| Serial1      |       +--------------+
                   |          SPI |<----->| SX1276 Radio |<---> Antenna
    USB Serial <-->| Serial       |       +--------------+         ^
                   +--------------+                                |
                                                                   |
                   +--------------+                                |
                   |     SAMD     |                                |
                   |              |                                |
    TTL Serial <-->| Serial1      |       +--------------+         V
                   |          SPI |<----->| SX1276 Radio |<---> Antenna
    USB Serial <-->| Serial       |       +--------------+
                   +--------------+

                          +--------------+
                          | SAMD         |
                          |              |
                          |      PB02 A5 |---> rxLED
                          |      PB23 31 |---> txLED
                          |              |
                          |      PA07  9 |---> rssi4LED
                          |      PA06  8 |---> rssi3LED
                          |      PA05 A4 |---> rssi2LED
                          |      PA04 A3 |---> rssi1LED
                          |              |
    USB_D- <------------->| 28 PA24      |
    USB_D+ <------------->| 29 PA25      |
                          |              |
                          |      PA15  5 |---> cs -----> LORA_CS/
                          |      PA17 13 |---> SCLK ---> SPI_SCK
                          |      PA16 11 |---> MOSI ---> SPI_PICO
                          |      PA19 12 |<--- MISO ---> SPI_POCI
                          |              |
    RTS-0 <------ rts <---| 38 PA13      |
    TX-0 <------- tx <----| 0  PA10      |
    RX-I_LV <---- rx ---->| 1  PA11      |
    CTS-I_LV <--- cts --->| 30 PB22      |
                          |              |
                          |      PA09  3 |---> rxen ---> LORA_RXEN
                          |      PA14  2 |---> txen ---> LORA_TXEN
                          |              |
                          |      PA18 10 |<--- dio1 <--- LORA_D1 (Freq Change)
                          |      PA21  7 |<--- dio0 <--- LORA_D0 (TX Done)
                          |              |
                          |      PA20  6 |---> rst ----> LORA_RST/
                          |              |
                          |      PA23 21 |---> SCL
                          |      PA22 20 |---> SDA
                          +--------------+
*/

//Initialize the LoRaSerial board
void samdBeginBoard()
{
  //Use ADC to check resistor divider
  pin_boardID = A2;

  pin_cs = 5;
  pin_dio0 = 7;  //aka A0
  pin_dio1 = 10; //aka A1
  pin_txen = 2;
  pin_rxen = 3;
  pin_rst = 6;
  pin_cts = 30;
  pin_rts = 38;
  pin_txLED = 31;
  pin_rxLED = A5;
  pin_rssi1LED = A3;
  pin_rssi2LED = A4;
  pin_rssi3LED = 8;
  pin_rssi4LED = 9;

  pin_trainButton = 4;

  pin_trigger = A0;
  pin_hop_timer = A1;

  //Flow control
  pinMode(pin_rts, OUTPUT);
  updateRTS(false); //Disable serial input until the radio starts

  pinMode(pin_cts, INPUT_PULLUP);

  //LEDs
  pinMode(pin_rssi1LED, OUTPUT);
  digitalWrite(pin_rssi1LED, LOW);
  pinMode(pin_rssi2LED, OUTPUT);
  digitalWrite(pin_rssi2LED, LOW);
  pinMode(pin_rssi3LED, OUTPUT);
  digitalWrite(pin_rssi3LED, LOW);
  pinMode(pin_rssi4LED, OUTPUT);
  digitalWrite(pin_rssi4LED, LOW);

  pinMode(pin_txLED, OUTPUT);
  digitalWrite(pin_txLED, LOW);
  pinMode(pin_rxLED, OUTPUT);
  digitalWrite(pin_rxLED, LOW);

  //Train button input
  pinMode(pin_trainButton, INPUT_PULLUP);

  //Debug
  pinMode(pin_trigger, OUTPUT);
  digitalWrite(pin_trigger, HIGH);
  pinMode(pin_hop_timer, OUTPUT);
  digitalWrite(pin_hop_timer, LOW);

  //Get average of board ID voltage divider
  int val = 0;
  for (int x = 0 ; x < 8 ; x++)
    val += analogRead(pin_boardID);
  val /= 8;

  //Convert ADC to volts
  float boardID = 3.3 * val / 1024;

  //Use ADC to check board ID resistor divider
  if (boardID > 1.64 * 0.95 && boardID < 1.64 * 1.05)
  {
    radioBand = 915;
    strcpy(platformPrefix, "SAMD21 1W 915MHz");
  }
  else if (boardID > 2.20 * 0.95 && boardID < 2.20 * 1.05)
  {
    radioBand = 433;
    strcpy(platformPrefix, "SAMD21 1W 433MHz");
  }
  else if (boardID > 2.48 * 0.95 && boardID < 2.48 * 1.05)
  {
    radioBand = 868;
    strcpy(platformPrefix, "SAMD21 1W 868MHz");
  }
  else
  {
    strcpy(platformPrefix, "SAMD21 1W");
  }
}

//Initialize the USB serial port and the UART
void samdBeginSerial(uint16_t serialSpeed)
{
  if (settings.usbSerialWait)
    //Wait for serial to come online for debug printing
    while (!Serial);

  Serial1.begin(serialSpeed);
}

//Initialize the watch dog timer
void samdBeginWDT()
{
  myWatchDog.setup(WDT_HARDCYCLE2S);  // Initialize WDT with 2s timeout
  petTimeout = 1800;
}

//Initilaize the EEPROM controller or simulation
void samdEepromBegin()
{
}

//Write any remaining data to EEPROM
void samdEepromCommit()
{
  EEPROM.commit();
}

//Perform the necessary action to "pet" the watch dog timer
void samdPetWDT()
{
  //This takes 4-5ms to complete
  myWatchDog.clear();
}

//Initialize the radio module
Module * samdRadio()
{
  return new Module(pin_cs, pin_dio0, pin_rst, pin_dio1);
}

//Determine if serial input data is available
bool samdSerialAvailable()
{
  return (Serial.available() || Serial1.available());
}

//Ensure that all serial output data has been sent over USB and via the UART
void samdSerialFlush()
{
  Serial.flush();
  Serial1.flush();
}

//Read in the serial input data
uint8_t samdSerialRead()
{
  byte incoming = 0;
  if (Serial.available())
    incoming = Serial.read();
  else if (Serial1.available())
    incoming = Serial1.read();
  return (incoming);
}

//Provide the serial output data to the USB layer or the UART TX FIFO
void samdSerialWrite(uint8_t value)
{
  Serial.write(value);
  Serial1.write(value);
}

//Reset the CPU
void samdSystemReset()
{
  NVIC_SystemReset();
}

//Get the CPU's unique ID value
void samdUniqueID(uint8_t * unique128_BitID)
{
  uint32_t id[UNIQUE_ID_BYTES / 4];

  //Read the CPU's unique ID value
  id[0] = *(uint32_t *)0x0080a00c;
  id[1] = *(uint32_t *)0x0080a040;
  id[2] = *(uint32_t *)0x0080a044;
  id[3] = *(uint32_t *)0x0080a048;

  memcpy(unique128_BitID, id, UNIQUE_ID_BYTES);
}

//Provide the hardware abstraction layer (HAL) interface
const ARCH_TABLE arch = {
  samdBeginBoard,             //beginBoard
  samdBeginSerial,            //beginSerial
  samdBeginWDT,               //beginWDT
  samdEepromBegin,            //eepromBegin
  samdEepromCommit,           //eepromCommit
  samdPetWDT,                 //petWDT
  samdRadio,                  //radio
  samdSerialAvailable,        //serialAvailable
  samdSerialFlush,            //serialFlush
  samdSerialRead,             //serialRead
  samdSerialWrite,            //serialWrite
  samdSystemReset,            //systemReset
  samdUniqueID,               //uniqueID
};

#endif  //__SAMD_H__
#endif  //ARDUINO_ARCH_SAMD
